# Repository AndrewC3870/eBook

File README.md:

# OpenBook
Fully functional E-book reader project!

## 🧾 Bill of Materials (BOM)

| Component | Link to buy | Datasheet |
|-----------|-------------|-----------|
|ESP32-C6   | [Mouser](https://ro.mouser.com/ProductDetail/Espressif-Systems/ESP32-C6-WROOM-1-N8?qs=8Wlm6%252BaMh8ST02Gmwp74cw%3D%3D) | [Datasheet](https://ro.mouser.com/datasheet/2/891/Espressif_ESP32_C6_WROOM_1__Datasheet_V0_1_PRELIMI-3239987.pdf)|
| E-Ink Display 7.5" 800x480 | [Waveshare](https://www.waveshare.com/7.5inch-e-paper.htm) | [Datasheet](https://files.waveshare.com/upload/6/60/7.5inch_e-Paper_V2_Specification.pdf) |
| SD Module | [Comet](https://store.comet.srl.ro/Catalogue/Product/43497/) | [Datasheet](https://store.comet.bg/download-file.php?id=8824)|
| Polymer Lithium-Ion Battery | [TME](https://www.tme.eu/en/details/accu-lp584174_cl/rechargeable-batteries/cellevia-batteries/l584174/) | [Datasheet](https://www.tme.eu/Document/e0683d8c34e6d878124489f71bffb6ee/cel0014.pdf)|
| RTC DS3231SN  | [Mouser](https://ro.mouser.com/ProductDetail/Analog-Devices-Maxim-Integrated/DS3231SN?qs=1eQvB6Dk1vhUlr8%2FOrV0Fw%3D%3D) | [Datasheet](https://ro.mouser.com/datasheet/2/609/DS3231-3421123.pdf)|
| Environmental Sensor BME688 | [Mouser](https://ro.mouser.com/ProductDetail/Bosch-Sensortec/BME688?qs=IS%252B4QmGtzzqQoVDscqwx3A%3D%3D) | [Datasheet](https://ro.mouser.com/datasheet/2/783/bst_bme688_fl000-2307034.pdf)|
| Li-Po Battery Charging Controller | [Mouser](https://ro.mouser.com/ProductDetail/Microchip-Technology/MCP73831T-3ACI-OT?qs=yUQqVecv4quInAWkk8YFWg%3D%3D) | [Datasheet](https://ro.mouser.com/datasheet/2/268/MCP73831_Family_Data_Sheet_DS20001984H-3441711.pdf)|
| LDO Regulator | [Mouser](https://ro.mouser.com/ProductDetail/Torex-Semiconductor/XC6220A331MR-G?qs=AsjdqWjXhJ8ZSWznL1J0gg%3D%3D) | [Datasheet](https://ro.mouser.com/datasheet/2/760/xc6220-3371556.pdf)|
| External NOR Flash (64MB) | [Mouser](https://ro.mouser.com/ProductDetail/Winbond/W25Q512JVEIQ?qs=l7cgNqFNU1jw6svr3at6tA%3D%3D) | [Datasheet](https://ro.mouser.com/datasheet/2/949/Winbond_W25Q512JV_Datasheet-3240039.pdf)|
| USB-C Connector | [Mouser](https://ro.mouser.com/ProductDetail/GCT/USB4110-GF-A?qs=KUoIvG%2F9IlYiZvIXQjyJeA%3D%3D) | [Datasheet](https://ro.mouser.com/datasheet/2/837/GCT_USB4110_Product_Drawing___20k_cycles-3455479.pdf)|
| Buttons (x3)  | [CoolBe](https://www.coolbe.ro/ro/products/5bad89f21436d4015a56b3cd?currency=RON&variant_id=5bad89f21436d4045a56b3cf&utm_productid=5bad89f21436d4015a56b3cd&gsAttrs=eyJyZWdpb24iOiJSTyJ9&utm_source=google&utm_medium=cpc&utm_campaign=21392812512&utm_term=cid-21392812512%2Cagi-163746055117%2Cadi-703343975184%2Ctid-pla-295222477609%2Cdev-c%2Creg-1011795%2Cmd-5bad89f21436d4045a56b3cf&gad_source=1&gclid=Cj0KCQjwkZm_BhDrARIsAAEbX1Gw4soI9mTCNlHM371LOuknVimSGw5EjBiUSS3x-zeZasRt9d13DSAaAt8mEALw_wcB) | [Datasheet](https://www.coolbe.ro/ro/products/5bad89f21436d4015a56b3cd?currency=RON&variant_id=5bad89f21436d4045a56b3cf&utm_productid=5bad89f21436d4015a56b3cd&gsAttrs=eyJyZWdpb24iOiJSTyJ9&utm_source=google&utm_medium=cpc&utm_campaign=21392812512&utm_term=cid-21392812512%2Cagi-163746055117%2Cadi-703343975184%2Ctid-pla-295222477609%2Cdev-c%2Creg-1011795%2Cmd-5bad89f21436d4045a56b3cf&gad_source=1&gclid=Cj0KCQjwkZm_BhDrARIsAAEbX1Gw4soI9mTCNlHM371LOuknVimSGw5EjBiUSS3x-zeZasRt9d13DSAaAt8mEALw_wcB)|
| Qwiic | [SPARKFUN](https://www.sparkfun.com/qwiic-jst-connector-smd-4-pin-horizontal.html) | [Datasheet](https://cdn.sparkfun.com/assets/parts/1/2/2/8/9/Qwiic_Connector_Datasheet.pdf)|
| Schottky Diodes | [Mouser](https://ro.mouser.com/ProductDetail/KYOCERA-AVX/SD0805S020S1R0?qs=jCA%252BPfw4LHbpkAoSnwrdjw%3D%3D) | [Datasheet](https://ro.mouser.com/datasheet/2/40/schottky-3165252.pdf)|
|Resistors | [Mouser](https://ro.mouser.com/c/?q=resistor%200402) | [Datasheet](https://ro.mouser.com/c/?q=resistor%200402)|
|USBLC6-2SC6Y | [Digikey](https://www.digikey.ro/ro/products/detail/stmicroelectronics/USBLC6-2SC6Y/2819177?s=N4IgTCBcDaIKoGUBCAZAwgNgLRgZgmiALoC%2BQA) | [Datasheet](https://www.st.com/content/ccc/resource/technical/document/datasheet/group0/94/15/6c/58/ba/91/46/42/DM00055262/files/DM00055262.pdf/jcr:content/translations/en.DM00055262.pdf)|
|Transistors | [Mouser](https://ro.mouser.com/ProductDetail/Diodes-Incorporated/DMG2305UX-7?qs=L1DZKBg7t5F%2FNBHrjfxC%252Bg%3D%3D) | [Datasheet](https://www.diodes.com/assets/Datasheets/DMG2305UX.pdf)|
|SMC Diode | [DigiKey](https://www.digikey.ro/ro/products/detail/smc-diode-solutions/MBR0530/16692306) | [Datasheet](https://www.smc-diodes.com/propdf/MBR0530%20N0717%20REV.A.pdf)|
|N-channel MOSFET | [DigiKey](https://www.digikey.ro/ro/products/detail/vishay-siliconix/SI1308EDL-T1-GE3/4876435?s=N4IgTCBcDaIMoEkCMBmADADgKIBEAyAtACpIEDiWKIAugL5A) | [Datasheet](https://www.vishay.com/docs/63399/si1308edl.pdf)|
|Display Connector | [Mouser](https://ro.mouser.com/ProductDetail/Hirose-Connector/FH34SRJ-24S-0.5SH99?qs=vcbW%252B4%252BSTIpKBl5ap9J8Fw%3D%3D) | [Datasheet](https://ro.mouser.com/datasheet/2/185/FH34SRJ_24S_0_5SH_99__CL0580_1255_6_99_2DDrawing_0-1615044.pdf)|
|Power Inductor | [Mouser](https://ro.mouser.com/ProductDetail/Bourns/SRR4828A-101M?qs=EU6FO9ffTwcw5i9FweW3JA%3D%3D) | [Datasheet](https://ro.mouser.com/datasheet/2/54/srr4828a-1391533.pdf)|

## 📊 Bloc Diagram and PCB

## 📗 Main Components and Connections
1. **Main processing unit**
    * `ESP32-C6 Microcontroller (ESP32-C6-WROOM-1-N8)` - The central processing unit of the system with WiFi/Bluetooth connectivity.

2. **Power Management System**
    * `LDO Voltage Regulator (XC6220A331MR-G)`: Provides stable 3.3V power from battery/USB

    * `Li-Po Battery Charging Controller (MCP73831)`: Manages charging of the LP584174 battery

    * `Battery Charge Level Monitoring (MAX17048G+T10)`: Connected via I2C to monitor battery status
3. **Display System**
    * `E-Ink Display (7.5" 800×480 px)`: Connected via SPI interface, displays the content

4. **Storage**
    * `External NOR Flash (W25Q512JVEIQ, 64MB)`: Connected via SPI, main memory 64 MB

    * `SD Card`: Connected via SPI, used for external memory extension for adding books

5. **Environmental Sensing**
    * `BME688 Environmental Sensor`: Connected via I2C used to detect a wide variety of volatile organic compounds

6. **Real-Time Clock**
    * `DS3231SN RTC Module`: Connected via I2C (same bus as BME688)measures and tracks time, often in hours, minutes, and seconds

7. **User Interface**
    * `Buttons`: 3x GPIO buttons (Reset, Change, Boot)

8. **Connectivity**
    * `USB-C Connector`: For power and programming
    * `Qwiic/Stemma QT Connector`: I2C expansion port

## 🛠️ ESP32-C6 Used pins

| PIN | Component | Signal Name | Notes|
|-----|----------|--------------------------|------|
| 3V3 | LDO Voltage Regulator | 3V3 | Supply power |
| EN | Reset Button | RESET| Reset in case of error |
| IO0| RTC Module | INT_RTC | High precision real time clock chip|
| IO1| RTC Module | 32KHZ| High precision real time clock chip|
| IO2| External NOR Flash, SD Card | MISO| Master In Slave Out|
| IO3| E-Paper Display | EPD_BUSY||
| IO4| SD Card | SS_SD | Extern memory (Micro SD cards)|
| IO5| E-Paper Display| EPD_DC||
| IO6| External NOR Flash, SD Card, E-Paper Display| SCK| SCK is the clock line for SPI communication|
| IO7| External NOR Flash, SD Card, E-Paper Display| MOSI|  Master Out Slave In|
| IO9| Boot Button | IO/BOOT| Boot|
| IO10| E-Paper Display | EPD_CS| for E-Ink display|
| IO11| External NOR Flash | FLASH_CS| |
| IO12| ESD protection | USB_D-| Protection against electrostatic discharges |
| IO13| ESD protection | USB_D+| Protection against electrostatic discharges |
| IO14| Change Button | IO/CHANGE| |
| IO15| Test Pads| TX| Transmit data|
| IO16| Test Pads | RX| Receive data|
| IO17| RTC Module | RTC_RST| |
| IO18| Environmental Sensor | I2C_PW|  To detect a wide variety of volatile organic compounds|
| IO19| EPD Power | EPD_3V3_C| Electronic power design|
| IO20| RTC Module, Qwiic / Stemma QT, Battery ChargeLevel| SDA| Transmit data to or from target devices|
| IO21| Battery ChargeLevel, Environmental Sensor, RTC Module, Qwiic / Stemma QT| SCL| Used to synchronously clock data in or out of the target device|
| IO22| E-Paper Display| EPD_RST| |
| GND| Ground | GND | Connected to the main ground|

## 🔋 Power Consumption Considerations
The system is designed for low power operation, because the most power consuming components are the screen and the ESP32-C6.

* E-Ink Display: Only consumes power during updates about **0.3mW**
* ESP32-C6: Can enter deep sleep mode **26.85 μW** between operations and the average power consumption during active mode is **78.32 mW**
* Battery 3.7V 1800mAh that is **6.6W** of power

The avarage lifetime of device is about 14-17 days!

## 🔄 Important updates
∘ Updated the 3d model of the case, maked the design more comfortable by adding smooth edges and a nice texture for better grip, also modified the interior size of the case to perfectly fit the components inside! 

∘ I have added some necessary files (a picture showing the arrangement of the components in the case, and the F3Z file with the complete design).

∘ In the future, the implementation of software that will allow the use of the eBook is expected.

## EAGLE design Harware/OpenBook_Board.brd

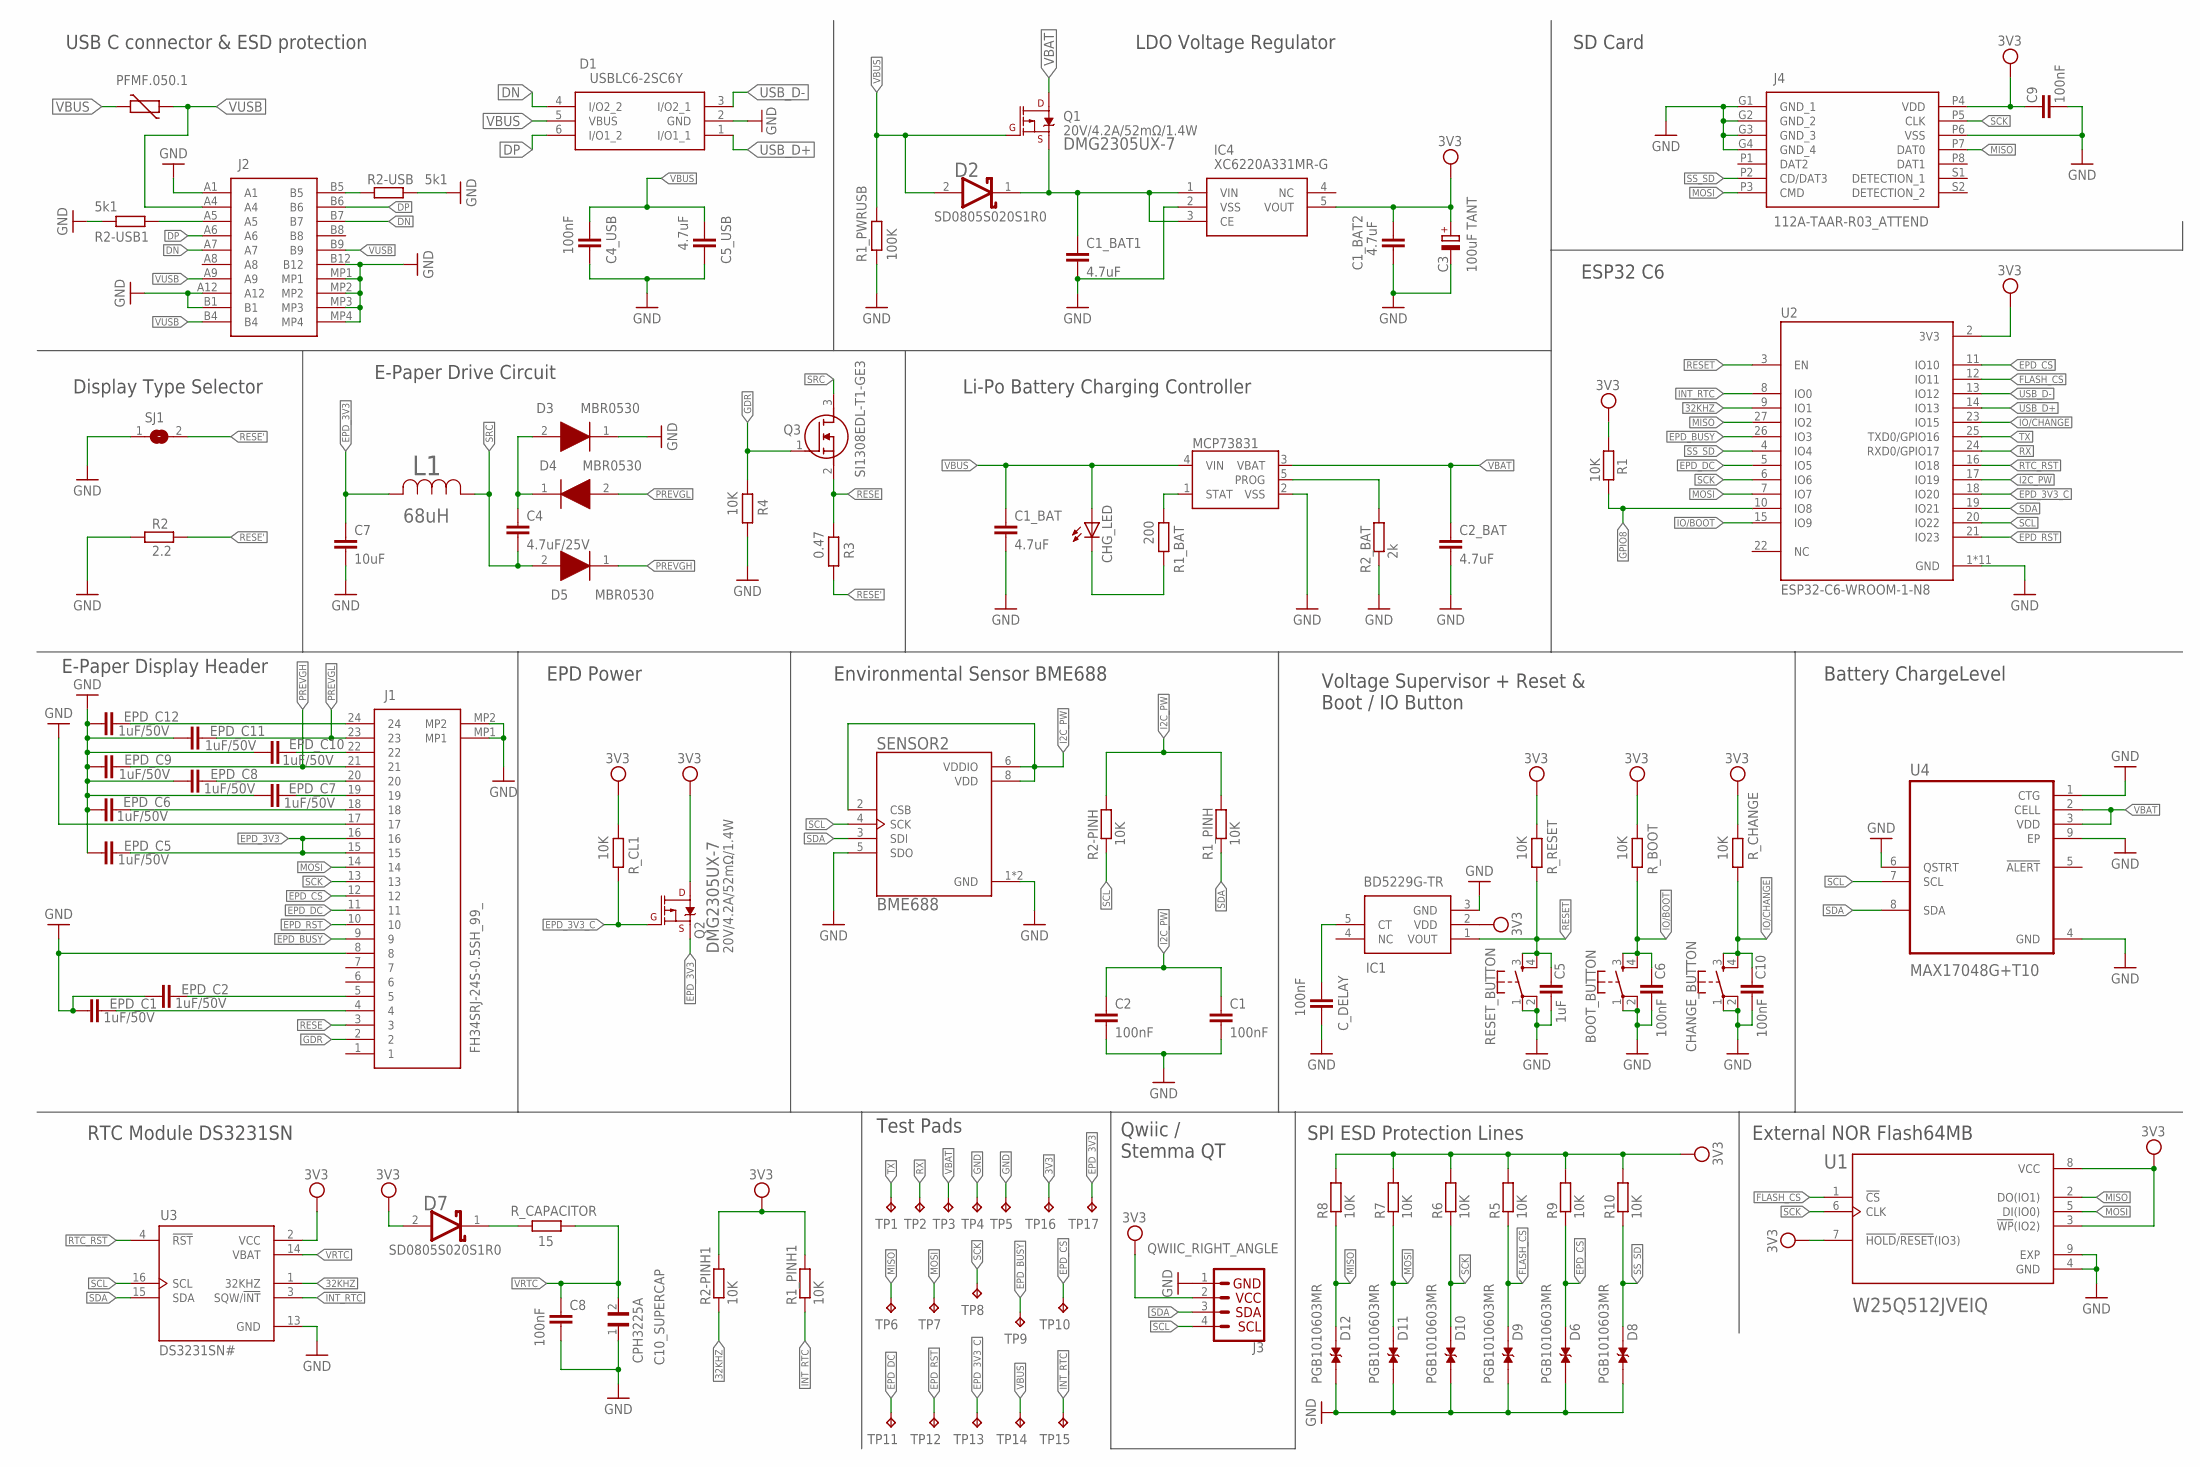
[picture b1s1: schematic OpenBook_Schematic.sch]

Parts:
BOOT_BUTTON: BUTTON_CUSYOMV1; MYBUTTON
C1, C2, C4_USB, C6, C8, C9, C10: 100nF; EAGLE-LTSPICE_C0402
C1_BAT, C1_BAT1, C1_BAT2, C2_BAT, C5_USB: 4.7uF; EAGLE-LTSPICE_C0402
C3: 100uF TANT; RCL_CT3528
C4: 4.7uF/25V; EAGLE-LTSPICE_C0402
C5: 1uF; EAGLE-LTSPICE_C0402
C7: 10uF; EAGLE-LTSPICE_C0402
C10_SUPERCAP: CPH3225A; CAPCP3225X100N
CHANGE_BUTTON: BUTTON_CUSYOMV1; MYBUTTON
CHG_LED: ADAFRUIT_LEDCHIP-LED0603; ADAFRUIT_CHIP-LED0603
C_DELAY: 100nF; EAGLE-LTSPICE_C0402
D1: USBLC6-2SC6Y; SOT95P280X145-6N
D2, D7: ESP32_WROVER_AVX---SD0805S020S1R0_AVX_SD0805S020S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; ESP32_WROVER_AVX---SD0805S020S1R0_AVX_SD0805S020S1R0_0
D3, D4, D5: MBR0530; SOD3716X135N
D6, D8, D9, D10, D11, D12: PGB1010603MR; DIOC1608X36N
EPD_C1, EPD_C2, EPD_C5, EPD_C6, EPD_C7, EPD_C8, EPD_C9, EPD_C10, EPD_C11, EPD_C12: 1uF/50V; EAGLE-LTSPICE_C0402
IC1: BD5229G-TR; SOT95P280X125-5N
IC4: XC6220A331MR-G; SOT95P280X120-5N
J1: FH34SRJ-24S-0.5SH_99_; FH34SRJ24S05SH99
J2: SAMACSYS_PARTS_USB4110-GF-A; SAMACSYS_PARTS_USB4110GFA
J3: QWIIC_RIGHT_ANGLE; JST04_1MM_RA
J4: 112A-TAAR-R03_ATTEND; 112ATAARR03ATTEND
L1: 744043680IND_4828-WE-TPC_WRE; IND_4828-WE-TPC_WRE
MCP73831: ESP32_WROVER_SPARKFUN-IC-POWER_MCP73831; ESP32_WROVER_SPARKFUN-IC-POWER_SOT23-5
PFMF.050.1: ESP32C6_VARISTORCN1812; ESP32C6_VARISTOR_CT/CN1812
Q1, Q2: 20V/4.2A/52mΩ/1.4W; ESP32_WROVER_SPARKFUN-DISCRETESEMI_SOT23-3
Q3: SI1308EDL-T1-GE3; SOT65P210X110-3N
R1, R1_PINH, R1_PINH1, R2-PINH, R2-PINH1, R4, R5, R6, R7, R8, R9, R10: 10K; ESP32_WROVER_EAGLE-LTSPICE_R0402
R1_BAT: 200; ESP32_WROVER_EAGLE-LTSPICE_R0402
R1_PWRUSB: 100K; ESP32_WROVER_EAGLE-LTSPICE_R0402
R2: 2.2; ESP32_WROVER_EAGLE-LTSPICE_R0402
R2-USB, R2-USB1: 5k1; ESP32_WROVER_EAGLE-LTSPICE_R0402
R2_BAT: 2k; ESP32_WROVER_EAGLE-LTSPICE_R0402
R3: 0.47; ESP32_WROVER_EAGLE-LTSPICE_R0402
RESET_BUTTON: BUTTON_CUSYOMV1; MYBUTTON
R_BOOT: 10K; ESP32_WROVER_EAGLE-LTSPICE_R0402
R_CAPACITOR: 15; ESP32_WROVER_EAGLE-LTSPICE_R0402
R_CHANGE: 10K; ESP32_WROVER_EAGLE-LTSPICE_R0402
R_CL1: 10K; ESP32_WROVER_EAGLE-LTSPICE_R0402
R_RESET: 10K; ESP32_WROVER_EAGLE-LTSPICE_R0402
SENSOR2: ESP32_WROVER_BME680_BME680; ESP32_WROVER_BME680_PSON80P300X300X100-8N
SJ1: SJ
TP1, TP2, TP3, TP4, TP5, TP6, TP7, TP8, TP9, TP10, TP11, TP12, TP13, TP14, TP15, TP16, TP17: TPTP20R; TP20R
U1: W25Q512JVEIQ; SON127P600X800X80-9N
U2: ESP32-C6-WROOM-1-N8; XCVR_ESP32-C6-WROOM-1-N8
U3: DS3231SN#; SOIC127P1032X265-16N
U4: MAX17048G+T10; SON50P200X200X80-9N

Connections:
3V3: C1_BAT2.2, C3.+, C9.2, D7.2 (ANODE), IC1.2 (VDD), IC4.5 (VOUT), J3.2, J4.P4 (VDD), Q2.3 (D), R1.1, R1_PINH1.2, R2-PINH1.2, R5.2, R6.2, R7.2, R8.2, R9.2, R10.2, R_BOOT.2, R_CHANGE.2, R_CL1.2, R_RESET.2, TP16.TP, U1.3 (!WP!(IO2)), U1.7 (!HOLD!/!RESET!(IO3)), U1.8 (VCC), U2.2 (3V3), U3.2 (VCC)
32KHZ: R2-PINH1.1, U2.9 (IO1), U3.1 (32KHZ)
DN: D1.4 (I/O2_2), J2.A7, J2.B7
DP: D1.6 (I/O1_2), J2.A6, J2.B6
EPD_3V3: C7.2, EPD_C5.1, J1.15, J1.16, L1.2, Q2.2 (S), TP17.TP
EPD_3V3_C: Q2.1 (G), R_CL1.1, TP13.TP, U2.18 (IO20)
EPD_BUSY: J1.9, TP9.TP, U2.26 (IO3)
EPD_CS: D6.2, J1.12, R9.1, TP10.TP, U2.11 (IO10)
EPD_DC: J1.11, TP11.TP, U2.5 (IO5)
EPD_RST: J1.10, TP12.TP, U2.21 (IO23)
FLASH_CS: D9.2, R5.1, U1.1 (!CS), U2.12 (IO11)
GDR: J1.2, Q3.1 (G), R4.2
GND: BOOT_BUTTON.1, BOOT_BUTTON.2, C1.1, C1_BAT.1, C1_BAT1.1, C1_BAT2.1, C2.1, C2_BAT.1, C3.-, C4_USB.1, C5.1, C5_USB.1, C6.1, C7.1, C8.2, C9.1, C10.1, C10_SUPERCAP.1, CHANGE_BUTTON.1, CHANGE_BUTTON.2, C_DELAY.1, D1.2 (GND), D3.1 (K), D6.1, D8.1, D9.1, D10.1, D11.1, D12.1, EPD_C1.2, EPD_C2.2, EPD_C5.2, EPD_C6.2, EPD_C7.2, EPD_C8.2, EPD_C9.2, EPD_C10.2, EPD_C11.2, EPD_C12.2, IC1.3 (GND), IC4.2 (VSS), J1.8, J1.17, J1.MP1, J1.MP2, J2.A1, J2.A12, J2.B1, J2.B12, J2.MP1, J2.MP2, J2.MP3, J2.MP4, J3.1, J4.G1 (GND_1), J4.G2 (GND_2), J4.G3 (GND_3), J4.G4 (GND_4), J4.P6 (VSS), MCP73831.2 (VSS), R1_PWRUSB.2, R2.1, R2-USB.2, R2-USB1.1, R2_BAT.1, R4.1, RESET_BUTTON.1, RESET_BUTTON.2, SENSOR2.1 (GND), SENSOR2.5 (SDO), SENSOR2.7 (GND), SJ1.1, TP4.TP, TP5.TP, U1.4 (GND), U1.9 (EXP), U2.1 (GND), U2.28 (GND), U2.29_1 (GND), U2.29_2 (GND), U2.29_3 (GND), U2.29_4 (GND), U2.29_5 (GND), U2.29_6 (GND), U2.29_7 (GND), U2.29_8 (GND), U2.29_9 (GND), U3.13 (GND), U4.1 (CTG), U4.4 (GND), U4.6 (QSTRT), U4.9 (EP)
GPIO8: R1.2, U2.10 (IO8)
I2C_PW: C1.2, C2.2, R1_PINH.2, R2-PINH.2, SENSOR2.2 (CSB), SENSOR2.6 (VDDIO), SENSOR2.8 (VDD), U2.17 (IO19)
INT_RTC: R1_PINH1.1, TP15.TP, U2.8 (IO0), U3.3 (SQW/!INT)
IO/BOOT: BOOT_BUTTON.3, BOOT_BUTTON.4, C6.2, R_BOOT.1, U2.15 (IO9)
IO/CHANGE: C10.2, CHANGE_BUTTON.3, CHANGE_BUTTON.4, R_CHANGE.1, U2.23 (IO15)
MISO: D12.2, J4.P7 (DAT0), R8.1, TP6.TP, U1.2 (DO(IO1)), U2.27 (IO2)
MOSI: D11.2, J1.14, J4.P3 (CMD), R7.1, TP7.TP, U1.5 (DI(IO0)), U2.7 (IO7)
unnamed: J2.A5, R2-USB1.2
unnamed: J2.B5, R2-USB.1
unnamed: C1_BAT1.2, D2.1 (CATHODE), IC4.1 (VIN), IC4.3 (CE), Q1.2 (S)
unnamed: C4.2, D3.2 (A), D4.1 (K)
unnamed: CHG_LED.C, R1_BAT.1
unnamed: MCP73831.1 (STAT), R1_BAT.2
unnamed: MCP73831.5 (PROG), R2_BAT.2
unnamed: EPD_C12.1, J1.24
unnamed: C_DELAY.2, IC1.5 (CT)
unnamed: EPD_C2.1, J1.5
unnamed: EPD_C10.1, J1.22
unnamed: EPD_C8.1, J1.20
unnamed: EPD_C7.1, J1.19
unnamed: EPD_C6.1, J1.18
unnamed: EPD_C1.1, J1.4
unnamed: D7.1 (CATHODE), R_CAPACITOR.2
PREVGH: D5.1 (K), EPD_C9.1, J1.21
PREVGL: D4.2 (A), EPD_C11.1, J1.23
RESE: J1.3, Q3.2 (S), R3.2
RESE': R2.2, R3.1, SJ1.2
RESET: C5.2, IC1.1 (VOUT), RESET_BUTTON.3, RESET_BUTTON.4, R_RESET.1, U2.3 (EN)
RTC_RST: U2.16 (IO18), U3.4 (!RST)
RX: TP2.TP, U2.24 (RXD0/GPIO17)
SCK: D10.2, J1.13, J4.P5 (CLK), R6.1, TP8.TP, U1.6 (CLK), U2.6 (IO6)
SCL: J3.4, R2-PINH.1, SENSOR2.4 (SCK), U2.20 (IO22), U3.16 (SCL), U4.7 (SCL)
SDA: J3.3, R1_PINH.1, SENSOR2.3 (SDI), U2.19 (IO21), U3.15 (SDA), U4.8 (SDA)
SRC: C4.1, D5.2 (A), L1.1, Q3.3 (D)
SS_SD: D8.2, J4.P2 (CD/DAT3), R10.1, U2.4 (IO4)
TX: TP1.TP, U2.25 (TXD0/GPIO16)
USB_D+: D1.1 (I/O1_1), U2.14 (IO13)
USB_D-: D1.3 (I/O2_1), U2.13 (IO12)
VBAT: C2_BAT.2, MCP73831.3 (VBAT), Q1.3 (D), TP3.TP, U4.2 (CELL), U4.3 (VDD)
VBUS: C1_BAT.2, C4_USB.2, C5_USB.2, CHG_LED.A, D1.5 (VBUS), D2.2 (ANODE), MCP73831.4 (VIN), PFMF.050.1.2, Q1.1 (G), R1_PWRUSB.1, TP14.TP
VRTC: C8.1, C10_SUPERCAP.2, R_CAPACITOR.1, U3.14 (VBAT)
VUSB: J2.A4, J2.A9, J2.B4, J2.B9, PFMF.050.1.1

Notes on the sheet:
USB C connector & ESD protection
LDO Voltage Regulator
SD Card
ESP32 C6
Li-Po Battery Charging Controller
E-Paper Display Header
Display Type Selector
E-Paper Drive Circuit
EPD Power
Environmental Sensor BME688
Voltage Supervisor + Reset & Boot / IO Button
Battery ChargeLevel
RTC Module DS3231SN
Test Pads
Qwiic / Stemma QT
SPI ESD Protection Lines
External NOR Flash64MB

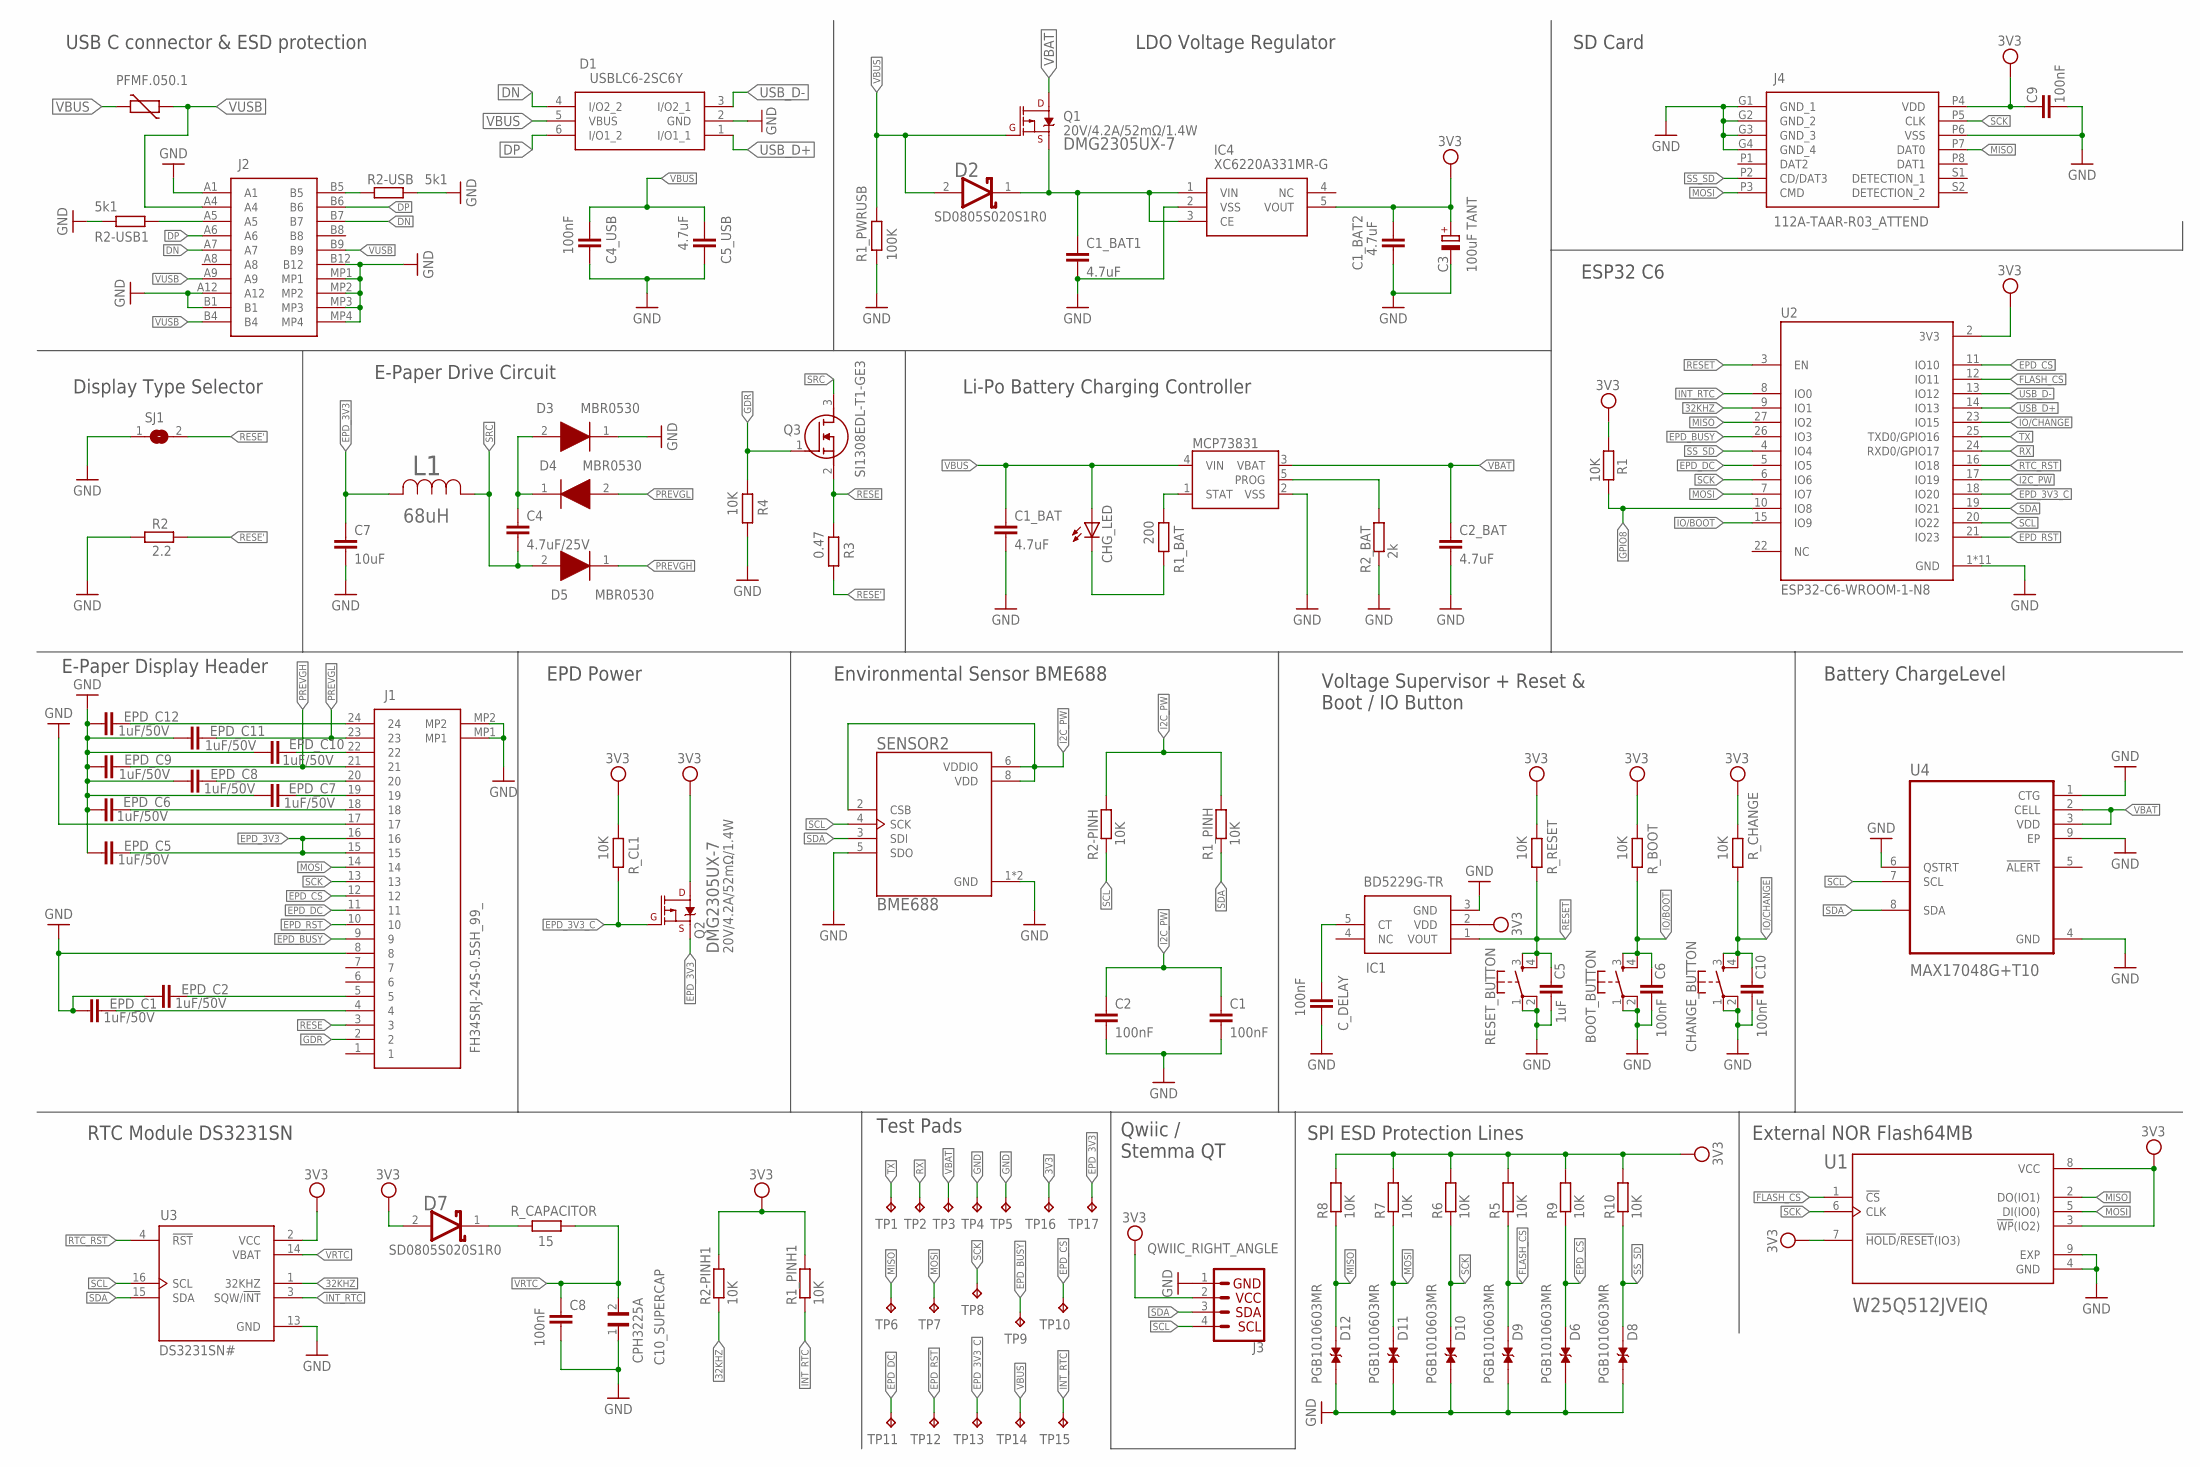
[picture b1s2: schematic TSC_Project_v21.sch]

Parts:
BOOT_BUTTON: BUTTON_CUSYOMV1; MYBUTTON
C1, C2, C4_USB, C6, C8, C9, C10: 100nF; EAGLE-LTSPICE_C0402
C1_BAT, C1_BAT1, C1_BAT2, C2_BAT, C5_USB: 4.7uF; EAGLE-LTSPICE_C0402
C3: 100uF TANT; RCL_CT3528
C4: 4.7uF/25V; EAGLE-LTSPICE_C0402
C5: 1uF; EAGLE-LTSPICE_C0402
C7: 10uF; EAGLE-LTSPICE_C0402
C10_SUPERCAP: CPH3225A; CAPCP3225X100N
CHANGE_BUTTON: BUTTON_CUSYOMV1; MYBUTTON
CHG_LED: ADAFRUIT_LEDCHIP-LED0603; ADAFRUIT_CHIP-LED0603
C_DELAY: 100nF; EAGLE-LTSPICE_C0402
D1: USBLC6-2SC6Y; SOT95P280X145-6N
D2, D7: ESP32_WROVER_AVX---SD0805S020S1R0_AVX_SD0805S020S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; ESP32_WROVER_AVX---SD0805S020S1R0_AVX_SD0805S020S1R0_0
D3, D4, D5: MBR0530; SOD3716X135N
D6, D8, D9, D10, D11, D12: PGB1010603MR; DIOC1608X36N
EPD_C1, EPD_C2, EPD_C5, EPD_C6, EPD_C7, EPD_C8, EPD_C9, EPD_C10, EPD_C11, EPD_C12: 1uF/50V; EAGLE-LTSPICE_C0402
IC1: BD5229G-TR; SOT95P280X125-5N
IC4: XC6220A331MR-G; SOT95P280X120-5N
J1: FH34SRJ-24S-0.5SH_99_; FH34SRJ24S05SH99
J2: SAMACSYS_PARTS_USB4110-GF-A; SAMACSYS_PARTS_USB4110GFA
J3: QWIIC_RIGHT_ANGLE; JST04_1MM_RA
J4: 112A-TAAR-R03_ATTEND; 112ATAARR03ATTEND
L1: 744043680IND_4828-WE-TPC_WRE; IND_4828-WE-TPC_WRE
MCP73831: ESP32_WROVER_SPARKFUN-IC-POWER_MCP73831; ESP32_WROVER_SPARKFUN-IC-POWER_SOT23-5
PFMF.050.1: ESP32C6_VARISTORCN1812; ESP32C6_VARISTOR_CT/CN1812
Q1, Q2: 20V/4.2A/52mΩ/1.4W; ESP32_WROVER_SPARKFUN-DISCRETESEMI_SOT23-3
Q3: SI1308EDL-T1-GE3; SOT65P210X110-3N
R1, R1_PINH, R1_PINH1, R2-PINH, R2-PINH1, R4, R5, R6, R7, R8, R9, R10: 10K; ESP32_WROVER_EAGLE-LTSPICE_R0402
R1_BAT: 200; ESP32_WROVER_EAGLE-LTSPICE_R0402
R1_PWRUSB: 100K; ESP32_WROVER_EAGLE-LTSPICE_R0402
R2: 2.2; ESP32_WROVER_EAGLE-LTSPICE_R0402
R2-USB, R2-USB1: 5k1; ESP32_WROVER_EAGLE-LTSPICE_R0402
R2_BAT: 2k; ESP32_WROVER_EAGLE-LTSPICE_R0402
R3: 0.47; ESP32_WROVER_EAGLE-LTSPICE_R0402
RESET_BUTTON: BUTTON_CUSYOMV1; MYBUTTON
R_BOOT: 10K; ESP32_WROVER_EAGLE-LTSPICE_R0402
R_CAPACITOR: 15; ESP32_WROVER_EAGLE-LTSPICE_R0402
R_CHANGE: 10K; ESP32_WROVER_EAGLE-LTSPICE_R0402
R_CL1: 10K; ESP32_WROVER_EAGLE-LTSPICE_R0402
R_RESET: 10K; ESP32_WROVER_EAGLE-LTSPICE_R0402
SENSOR2: ESP32_WROVER_BME680_BME680; ESP32_WROVER_BME680_PSON80P300X300X100-8N
SJ1: SJ
TP1, TP2, TP3, TP4, TP5, TP6, TP7, TP8, TP9, TP10, TP11, TP12, TP13, TP14, TP15, TP16, TP17: TPTP20R; TP20R
U1: W25Q512JVEIQ; SON127P600X800X80-9N
U2: ESP32-C6-WROOM-1-N8; XCVR_ESP32-C6-WROOM-1-N8
U3: DS3231SN#; SOIC127P1032X265-16N
U4: MAX17048G+T10; SON50P200X200X80-9N

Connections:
3V3: C1_BAT2.2, C3.+, C9.2, D7.2 (ANODE), IC1.2 (VDD), IC4.5 (VOUT), J3.2, J4.P4 (VDD), Q2.3 (D), R1.1, R1_PINH1.2, R2-PINH1.2, R5.2, R6.2, R7.2, R8.2, R9.2, R10.2, R_BOOT.2, R_CHANGE.2, R_CL1.2, R_RESET.2, TP16.TP, U1.3 (!WP!(IO2)), U1.7 (!HOLD!/!RESET!(IO3)), U1.8 (VCC), U2.2 (3V3), U3.2 (VCC)
32KHZ: R2-PINH1.1, U2.9 (IO1), U3.1 (32KHZ)
DN: D1.4 (I/O2_2), J2.A7, J2.B7
DP: D1.6 (I/O1_2), J2.A6, J2.B6
EPD_3V3: C7.2, EPD_C5.1, J1.15, J1.16, L1.2, Q2.2 (S), TP17.TP
EPD_3V3_C: Q2.1 (G), R_CL1.1, TP13.TP, U2.18 (IO20)
EPD_BUSY: J1.9, TP9.TP, U2.26 (IO3)
EPD_CS: D6.2, J1.12, R9.1, TP10.TP, U2.11 (IO10)
EPD_DC: J1.11, TP11.TP, U2.5 (IO5)
EPD_RST: J1.10, TP12.TP, U2.21 (IO23)
FLASH_CS: D9.2, R5.1, U1.1 (!CS), U2.12 (IO11)
GDR: J1.2, Q3.1 (G), R4.2
GND: BOOT_BUTTON.1, BOOT_BUTTON.2, C1.1, C1_BAT.1, C1_BAT1.1, C1_BAT2.1, C2.1, C2_BAT.1, C3.-, C4_USB.1, C5.1, C5_USB.1, C6.1, C7.1, C8.2, C9.1, C10.1, C10_SUPERCAP.1, CHANGE_BUTTON.1, CHANGE_BUTTON.2, C_DELAY.1, D1.2 (GND), D3.1 (K), D6.1, D8.1, D9.1, D10.1, D11.1, D12.1, EPD_C1.2, EPD_C2.2, EPD_C5.2, EPD_C6.2, EPD_C7.2, EPD_C8.2, EPD_C9.2, EPD_C10.2, EPD_C11.2, EPD_C12.2, IC1.3 (GND), IC4.2 (VSS), J1.8, J1.17, J1.MP1, J1.MP2, J2.A1, J2.A12, J2.B1, J2.B12, J2.MP1, J2.MP2, J2.MP3, J2.MP4, J3.1, J4.G1 (GND_1), J4.G2 (GND_2), J4.G3 (GND_3), J4.G4 (GND_4), J4.P6 (VSS), MCP73831.2 (VSS), R1_PWRUSB.2, R2.1, R2-USB.2, R2-USB1.1, R2_BAT.1, R4.1, RESET_BUTTON.1, RESET_BUTTON.2, SENSOR2.1 (GND), SENSOR2.5 (SDO), SENSOR2.7 (GND), SJ1.1, TP4.TP, TP5.TP, U1.4 (GND), U1.9 (EXP), U2.1 (GND), U2.28 (GND), U2.29_1 (GND), U2.29_2 (GND), U2.29_3 (GND), U2.29_4 (GND), U2.29_5 (GND), U2.29_6 (GND), U2.29_7 (GND), U2.29_8 (GND), U2.29_9 (GND), U3.13 (GND), U4.1 (CTG), U4.4 (GND), U4.6 (QSTRT), U4.9 (EP)
GPIO8: R1.2, U2.10 (IO8)
I2C_PW: C1.2, C2.2, R1_PINH.2, R2-PINH.2, SENSOR2.2 (CSB), SENSOR2.6 (VDDIO), SENSOR2.8 (VDD), U2.17 (IO19)
INT_RTC: R1_PINH1.1, TP15.TP, U2.8 (IO0), U3.3 (SQW/!INT)
IO/BOOT: BOOT_BUTTON.3, BOOT_BUTTON.4, C6.2, R_BOOT.1, U2.15 (IO9)
IO/CHANGE: C10.2, CHANGE_BUTTON.3, CHANGE_BUTTON.4, R_CHANGE.1, U2.23 (IO15)
MISO: D12.2, J4.P7 (DAT0), R8.1, TP6.TP, U1.2 (DO(IO1)), U2.27 (IO2)
MOSI: D11.2, J1.14, J4.P3 (CMD), R7.1, TP7.TP, U1.5 (DI(IO0)), U2.7 (IO7)
unnamed: J2.A5, R2-USB1.2
unnamed: J2.B5, R2-USB.1
unnamed: C1_BAT1.2, D2.1 (CATHODE), IC4.1 (VIN), IC4.3 (CE), Q1.2 (S)
unnamed: C4.2, D3.2 (A), D4.1 (K)
unnamed: CHG_LED.C, R1_BAT.1
unnamed: MCP73831.1 (STAT), R1_BAT.2
unnamed: MCP73831.5 (PROG), R2_BAT.2
unnamed: EPD_C12.1, J1.24
unnamed: C_DELAY.2, IC1.5 (CT)
unnamed: EPD_C2.1, J1.5
unnamed: EPD_C10.1, J1.22
unnamed: EPD_C8.1, J1.20
unnamed: EPD_C7.1, J1.19
unnamed: EPD_C6.1, J1.18
unnamed: EPD_C1.1, J1.4
unnamed: D7.1 (CATHODE), R_CAPACITOR.2
PREVGH: D5.1 (K), EPD_C9.1, J1.21
PREVGL: D4.2 (A), EPD_C11.1, J1.23
RESE: J1.3, Q3.2 (S), R3.2
RESE': R2.2, R3.1, SJ1.2
RESET: C5.2, IC1.1 (VOUT), RESET_BUTTON.3, RESET_BUTTON.4, R_RESET.1, U2.3 (EN)
RTC_RST: U2.16 (IO18), U3.4 (!RST)
RX: TP2.TP, U2.24 (RXD0/GPIO17)
SCK: D10.2, J1.13, J4.P5 (CLK), R6.1, TP8.TP, U1.6 (CLK), U2.6 (IO6)
SCL: J3.4, R2-PINH.1, SENSOR2.4 (SCK), U2.20 (IO22), U3.16 (SCL), U4.7 (SCL)
SDA: J3.3, R1_PINH.1, SENSOR2.3 (SDI), U2.19 (IO21), U3.15 (SDA), U4.8 (SDA)
SRC: C4.1, D5.2 (A), L1.1, Q3.3 (D)
SS_SD: D8.2, J4.P2 (CD/DAT3), R10.1, U2.4 (IO4)
TX: TP1.TP, U2.25 (TXD0/GPIO16)
USB_D+: D1.1 (I/O1_1), U2.14 (IO13)
USB_D-: D1.3 (I/O2_1), U2.13 (IO12)
VBAT: C2_BAT.2, MCP73831.3 (VBAT), Q1.3 (D), TP3.TP, U4.2 (CELL), U4.3 (VDD)
VBUS: C1_BAT.2, C4_USB.2, C5_USB.2, CHG_LED.A, D1.5 (VBUS), D2.2 (ANODE), MCP73831.4 (VIN), PFMF.050.1.2, Q1.1 (G), R1_PWRUSB.1, TP14.TP
VRTC: C8.1, C10_SUPERCAP.2, R_CAPACITOR.1, U3.14 (VBAT)
VUSB: J2.A4, J2.A9, J2.B4, J2.B9, PFMF.050.1.1

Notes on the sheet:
USB C connector & ESD protection
LDO Voltage Regulator
SD Card
ESP32 C6
Li-Po Battery Charging Controller
E-Paper Display Header
Display Type Selector
E-Paper Drive Circuit
EPD Power
Environmental Sensor BME688
Voltage Supervisor + Reset & Boot / IO Button
Battery ChargeLevel
RTC Module DS3231SN
Test Pads
Qwiic / Stemma QT
SPI ESD Protection Lines
External NOR Flash64MB

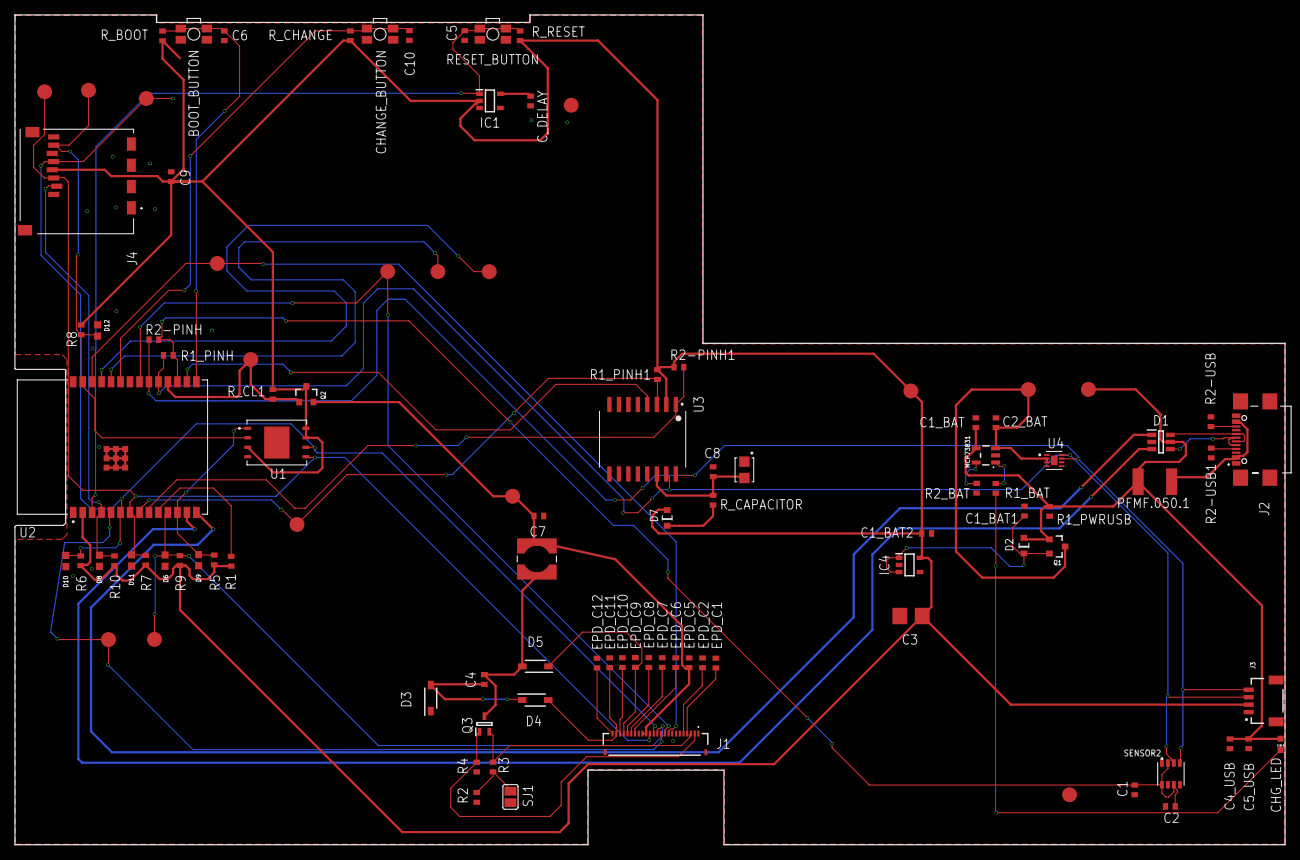
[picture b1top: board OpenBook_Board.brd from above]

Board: 2 copper layers, 170.2 x 111.2 mm, 103 parts (0 on the bottom side), 55 nets.

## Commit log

2025-03-23 added sch, brd and 3d model of ebook
2025-03-25 added the 3d model of battery and screen
2025-03-25 finished the 3d model of OpenBook v7
2025-03-25 added images
2025-03-25 updated the images, pcb and 3d designs
2025-03-25 new PCB image
2025-03-25 fixed issues and updated componets
2025-03-28 refactor all the circuit and added renders, step files
2025-03-30 Redacted the README
2025-03-30 Modified the README
2025-03-30 ReadMe
2025-03-30 modify README
2025-03-30 Create LICENSE
2025-04-01 Added the manufacture
2025-04-06 modified the thicknes of the pcb
2025-04-11 fixed issues
2025-04-11 added image with the components inside

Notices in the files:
parts and their libraries:
COPYRIGHT: Copyright (C) 2024 Ultra Librarian. All rights reserved.
